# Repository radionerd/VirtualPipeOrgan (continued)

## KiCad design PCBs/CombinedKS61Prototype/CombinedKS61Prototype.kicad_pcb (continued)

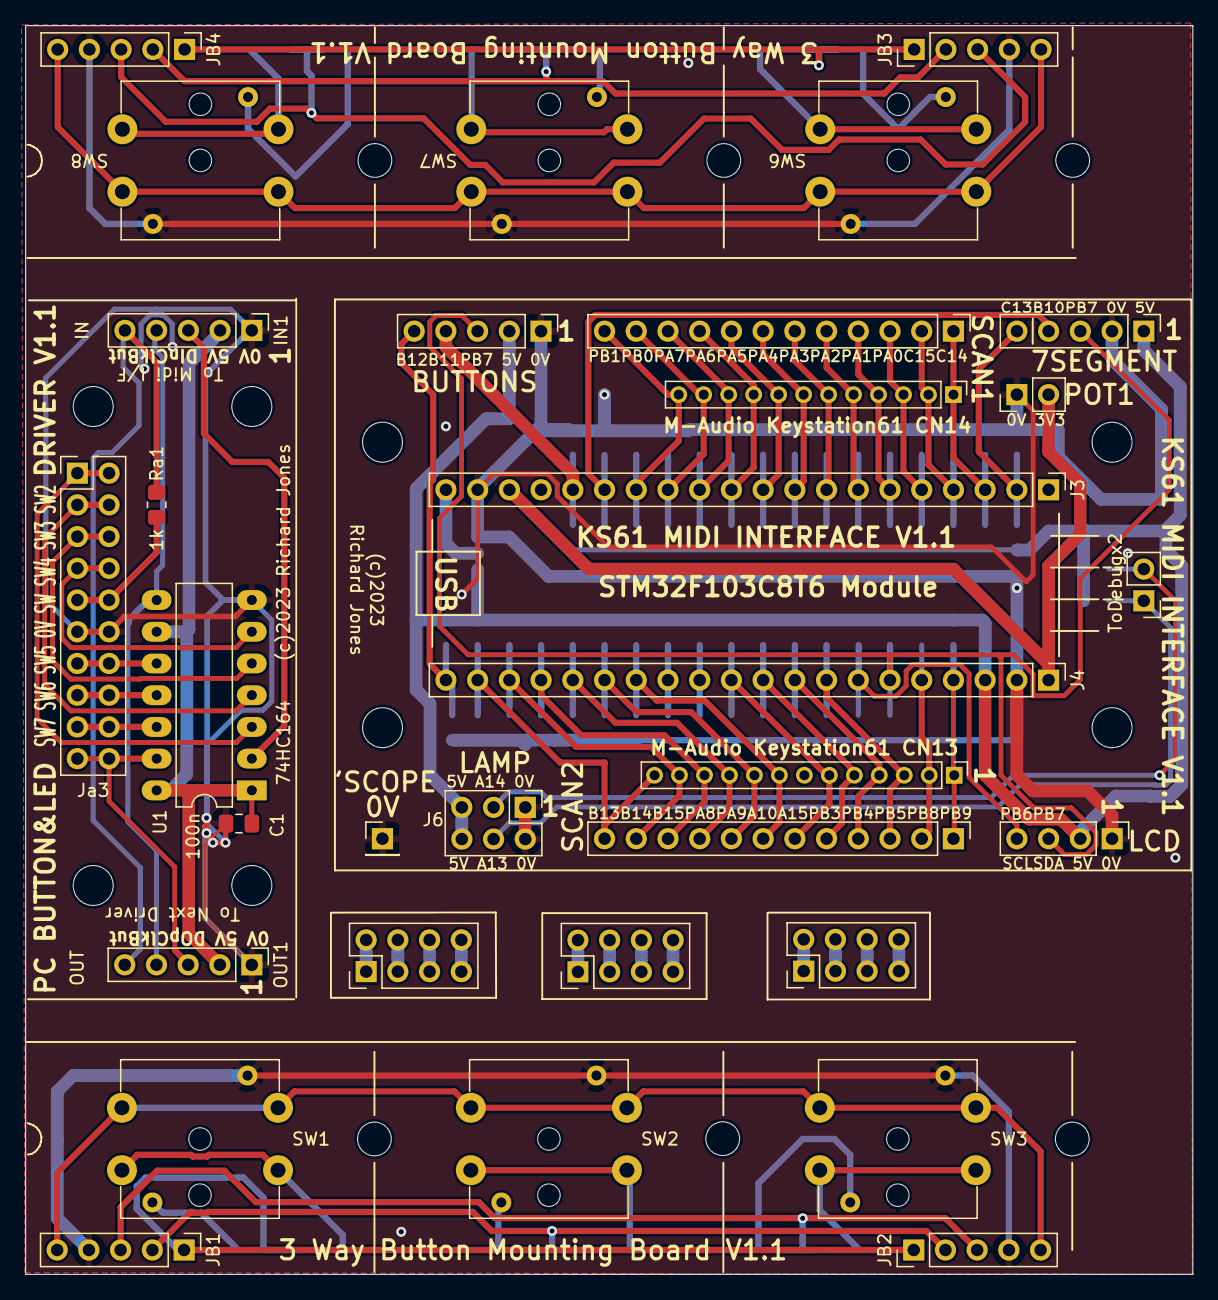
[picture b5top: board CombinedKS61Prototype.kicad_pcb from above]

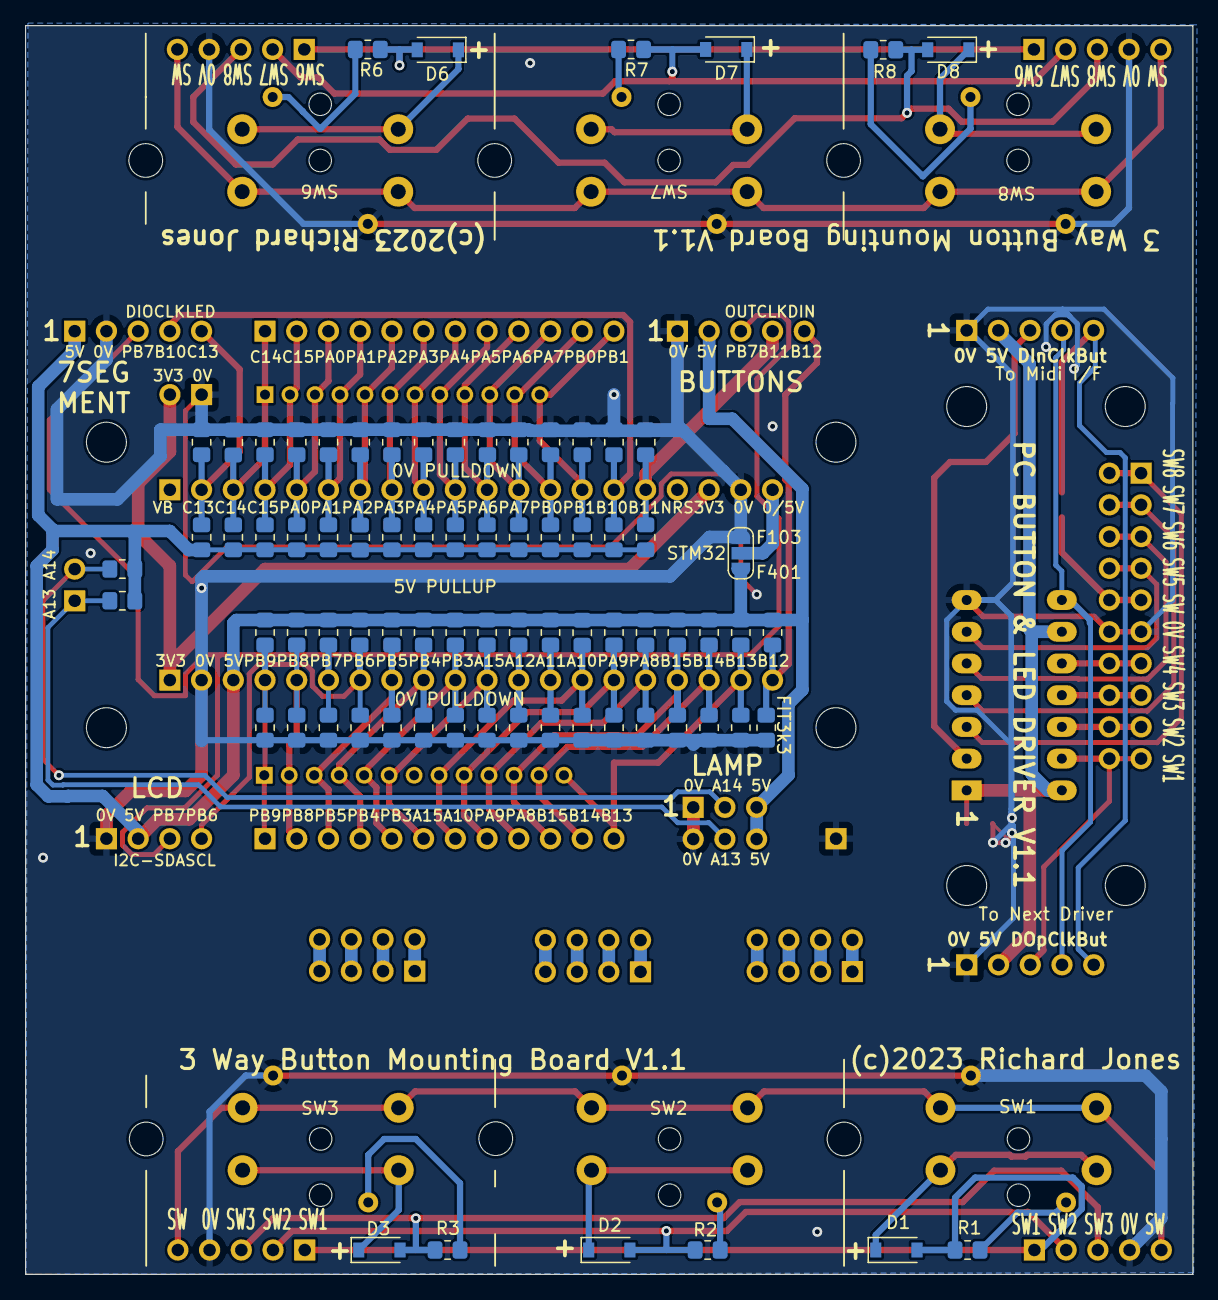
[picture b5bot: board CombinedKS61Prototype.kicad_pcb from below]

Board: 2 copper layers, 93.5 x 100.0 mm, 125 parts (79 on the bottom side), 83 nets.

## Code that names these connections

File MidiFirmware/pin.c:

#include <Arduino.h>
#include "pin.h"

const GPIOPinAssignment pinCfg[43]  = {
  // ordered in sequence around the PCB to assist wiring up
  // Rationale for pin assignment:
  // ADC 1-8, I2C and LED are predefined
  // All digital inputs are chosen to be 5V tolerant (makes driving from 5V shift registers a future option)
  // Scan inputs grouped together
  // shift register io are grouped together
  // scan outputs assigned in ascending sequence
  // STM32 IC Pins 1-22,7
  { VBAT, "VBAT", IO_RESERVED,0 },
  { PC13, "PC13", OP_LED  ,0 }, // OP1 PCB LED active low. Sink max 3mA, Source 3mA, Not 5V Tolerant
  { PC14, "PC14", OP_SCAN,7 }, // CN14  1 OUT
  { PC15, "PC15", OP_SCAN,6 }, // CN14  2 OUT 
  { PA0, "PA_0" , OP_SCAN,5 }, // CN14  3 OUT
  { PA1, "PA_1" , OP_SCAN,4 }, // CN14  4 OUT
  { PA2, "PA_2" , IP_SCAN,15 }, // CN14  5 IN
  { PA3, "PA_3" , IP_SCAN,14 }, // CN14  6 IN
  { PA4, "PA_4" , IP_SCAN,13 }, // CN14  7 IN 
  { PA5, "PA_5" , IP_SCAN,12 }, // CN14  8 IN 
  { PA6, "PA_6" , IP_SCAN,11 }, // CN14  9 IN 
  { PA7, "PA_7" , IP_SCAN,10 }, // CN14 10 IN 
  { PB0, "PB_0" , IP_SCAN,9 }, // CN14 11 IN 
  { PB1, "PB_1" , IP_SCAN,8 }, // CN14 12 IN 
  { PB10, "PB10" ,TM1637_CK,0 },
  { PB11, "PB11" ,OP_SR_CLOCK, NUM_SHIFT_REGISTER_BITS }, // CLK  Buttons  74HC164
  { NRST, "NRST", IO_RESERVED,0 }, 
  { V3_3, "3V3" , IO_RESERVED,0 },
  {  GND, "GND" , IO_RESERVED,0 },
  {  GND, "GND" , IO_RESERVED,0 },
  // STM32 IC Pins 25-46
  { PB12, "PB12", IP_SR_DATA,0 }, // DIN Buttons
  { PB13, "PB13", IP_SCAN,0x0 }, // CN13 13 IN
  { PB14, "PB14", IP_SCAN,0x1 }, // CN13 12 IN
  { PB15, "PB15", IP_SCAN,0x2 }, // CN13 11 IN
  { PA8,  "PA_8", IP_SCAN,0x3 }, // CN13 10 IN
  { PA9,  "PA_9", IP_SCAN,0x4 }, // CN13  9 IN
  { PA10, "PA10", IP_SCAN,0x5 }, // CN13  8 IN
  { PA11, "PA11", USB_M,0 },
  { PA12, "PA12", USB_P,0 },
  { PA15, "PA15", IP_SCAN,6 }, // CN13  6 IN
  { PB3,  "PB_3", IP_SCAN,7 }, // CN13  5 IN
  { PB4,  "PB_4", OP_SCAN,0 }, // CN13  4 OUT
  { PB5,  "PB_5", OP_SCAN,1 }, // CN13  3 OUT
  { PB6,  "PB_6", I2C_SCL,0 }, // I2C SCL1 LCD Displays
  { PB7,  "PB_7", I2C_SDA,0 }, // I2C SDA1 LCD Displays and SR_DATA combined. 4094 Pin 2 Shift registers are used for button input and associated LED indicator output
  { PB8,  "PB_8", OP_SCAN,2 }, // CN13  2 OUT
  { PB9,  "PB_9", OP_SCAN,3 }, // CN13  1 OUT
  { V5 ,  "+5V" , IO_RESERVED,0 },
  { GND , "GND",  IO_RESERVED,0 },
  { V3_3, "3V3",  IO_RESERVED,0 },
  { PA13, "PA13", SWDIO,0 }, // SWDIO - Located on Debug connector - Install boot loader before using for GPIO
  { PA14, "PA14", SWCLK,0 }, // SWCLK - Located on Debug connector - Install boot loader before using for GPIO
  { PB2,  "PB_2", BOOT1,0 }, // Boot1 - To use for GPIO remove Boot 1 link, and short R10 (100k) using 270R resistor
};

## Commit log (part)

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2023-08-24 Added round spacer washers to bracket
2023-08-24 Added generated dxf output files
2023-09-04 V1.0 PCB designs
2023-09-29 Console Drawings update following test cut, main cutting and assembly: 1 Reduce button cutout 17mm -> 14.5mm square 2 Rename trays trayI, trayII, trayIII 3 Add 9mm to trayII, 18mm to trayI 4 Add 4 fi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
2023-09-30 V1.1 PCB updates after initial testing 1. Share data out line between LCD, 7 Segment and button scan to yield spare io lines for control of WS8212 LEDs for music stand lamp 2. Replace level shifting 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
2025-04-20 Updates during initial console construction
2025-04-21 Added expression pedal drawings
2025-04-21 Add Maudio Keystation 61 Mk3 connector wiring and scan libreoffice document
2025-04-21 Archive midi firmware
2025-04-21 Add Assembly Notes
2025-04-23 Documentation updates
2025-04-23 Documentation qwerty update
2025-04-23 Block Diagram with transparent background
2025-04-24 Add stm32 port bit assignments, generate pdf
2025-04-24 Added pedalboard comment
2025-04-26 User interface preparation for pedalboard, adc and ws2812 support
2025-05-14 Add support for WS2812 LED strip Add support for scannned pedalboard Add support for 0-8 expression pedals Add Button LED invert feature Start UserManual.md
2025-05-14 Used manual partial update
2025-05-16 Refactor metronome display Update Readme and UserManual
2025-05-16 Fix Metronome Tempo display
2025-05-17 Extend Todo
2025-05-17 ✓Disable save of J[] monitor config to avoid startup issues ✓Display 0 ADCs when not in pedalboard mode ✓Configure Velocity Disable independent from pedalboard ✓Enhancement - Dim buttons when not ful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
2025-05-18 Improved profile feature Simple scheduler so that keyboard, buttons, lcds avoid each other in time
2025-05-18 Doc updates, added autoconnect script
2025-05-23 Buttons always scanned. Config LEDs dim/off, LEDs normal/invert check 100kHz vs 400KHz etc i2c lcd load timing 8.4ms vs 2.2ms Check button profile when midi not running vs running-Slow when GO not co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
2025-05-27 Adopt multi lcd code avoiding redundant writes down to character level Remove all warnings Profile Midi out to midi in Sysex response Make start sequence more informative and responsive
2025-06-02 Add Button LED to Midi Event monitor Add time to event monitor Fix pin configuration display for shift registers Add PC/USB Comms to LCD start screens Disble LCDs when not configured 7 seg display ad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
2025-06-03 Monitor Note to show middle C note 60 Octave 4, agree with midisnoop Activate up to 4 ADC inputs when Keyboard Velocity disabled Increase number of shift registers to 8
2025-06-04 LCD startup & print buffer updates
2025-06-04 Tidy up reporting of fault i2c bus Scheduler and timing offset by profile ID
2025-06-05 WS2812 Control on Lowest sharp when other notes silent for 5 seconds
2025-06-07 Investigate HID codes ready for page turning support Investigate and fix bad profile of WS2812 LED strip
2025-06-09 Fix timing discrepancy on WS2812 profile Reduce Midi channel config to 3 bits Reduce 74HC168 Config item to single 2 bit Add Page Turning control to configuration as 'H' command
2025-06-11 USB HID Page Turning feature complete
2025-06-13 Refactored colorwheel to WS2812Ctrl class Added status and event monitor to ws2812Ctrl Fixed profile of HID page turning
2025-06-15 Minor fixes and UserManual update
2025-06-18 Added MidiFirmware/Tools with Makefile and binaries for loading Flash
2025-07-09 comment update
2025-07-22 UI changed Midi to MIDI, Suppress repeat MIDI On or MIDI OFF on same note
